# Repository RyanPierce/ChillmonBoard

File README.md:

ChillmonBoard
=============

Chillmon Board

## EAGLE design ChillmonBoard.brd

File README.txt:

Chillmon Board v0.1
Copyright 2013 Ryan Pierce, rdpierce@pobox.com
https://github.com/RyanPierce/ChillmonBoard

Component RASPBERRYPI_B / RASBERRYPI_SHIELD modified from microBuilder
library, available at
http://www.microbuilder.eu/Projects/EagleFootprintLibrary.aspx

OVERVIEW

This board is a Raspberry Pi shield designed to be used with the Chillmon
application, available on Github at https://github.com/eastein/chillmon for 
the purposes of providing temperature control for fermenting beer!

INPUTS

J1-J8 are analog temperature sensors. The center pin is the signal, and the
end pins are power (+3.3V) and Ground. Power is indicated with the + 
symbol.

Each sensor connects to a channel on an MCP3008 10-bit ADC. This is 
connected to the Raspberry Pi as per the Adafruit tutorial available
here: http://learn.adafruit.com/send-raspberry-pi-data-to-cosm
Note that 4 of the Pi's GPIO pins are used for bit-banging SPI; the Pi's
native SPI is not used.

JP1 is a 0.1" header to determine the Vref voltage for the ADC conversion.
Two choices are provided; jumpering the left two pins provides a precision
1.0V reference, while jumpering the right two pins connects the 3.3V power
supply from the Pi. The regulation of this power supply is unknown. Using
1.0V leads to a lower temperature range (maximum is 50C / 122F) but provides
for a higher temperature resolution.

JP9 is a port for a chain of Dallas Semiconductor OneWire temperature
sensors, especially the DS18B20. Adafruit provides a tutorial here:
http://learn.adafruit.com/adafruits-raspberry-pi-lesson-11-ds18b20-temperature-sensing
As above, the center pin is the signal, and the end pins are power and 
ground. Power is marked with a + symbol. Many DS18B20's can be connected in
parallel. Note that the Adafruit Occidentalis distribution for the Raspberry
Pi includes the OneWire kernel driver. At present, the Chillmon software
does not support this. The board includes the 4.7k pullup resistor, which
is required for OneWire.

OUTPUTS

J10, J11, and J12 are digital outputs connected to GPIO pins on the Pi,
specifically GPIO17, GPIO21 (for Rev1 Pi) / GPIO27 (for Rev2 Pi), and
GPIO22 respectively. Rumor has it that the change between Rev1 and Rev2
is corrected within the Python library. Each pin has a 10k pulldown resistor, 
which is critical because the Pi initializes all pins in input mode; voltage
on them can float high enough to trigger solid state relays, which will
quickly burn out an  air conditioner compressor. Currently, the Chillmon
software assumes an air conditioner is connected to J10, however in the
future we would like to add a heater, as we have found that the temperature
at Pumping Station: One in the winter often drops below our target ale
fermenting temperature. Note that these outputs are current limited by the
Pi; it can directly drive a solid state relay.

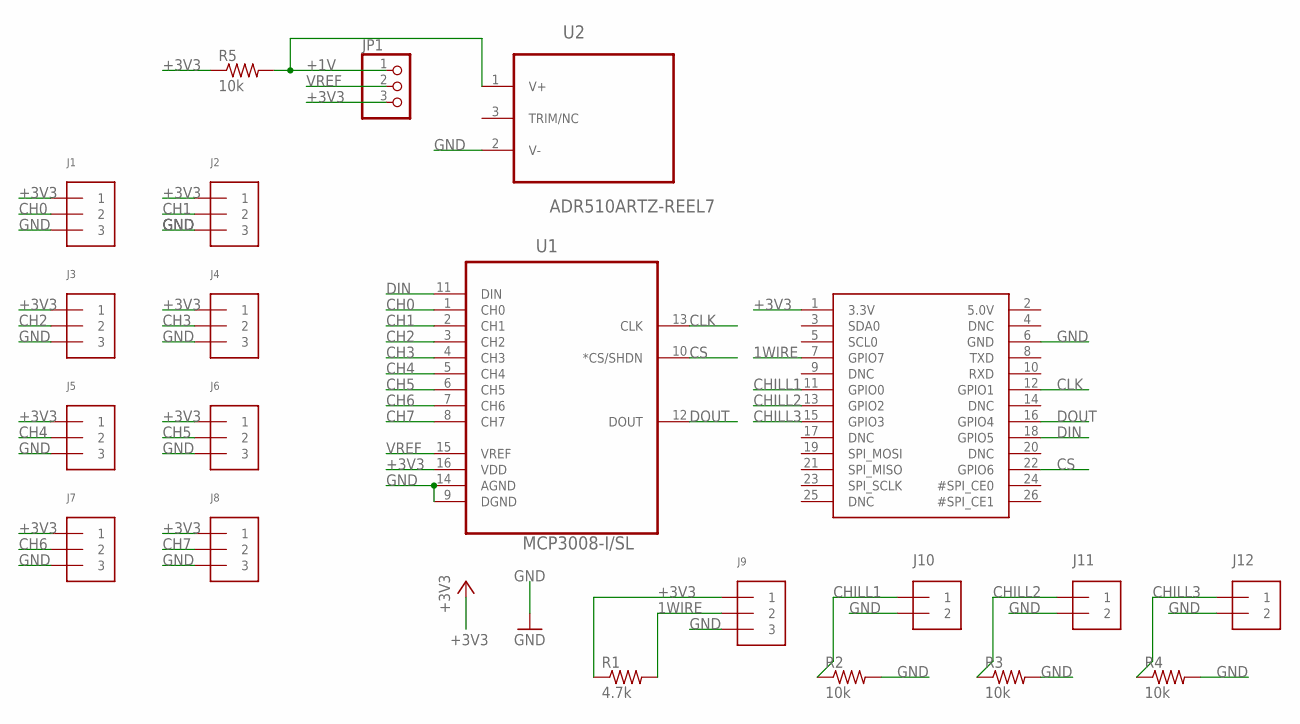
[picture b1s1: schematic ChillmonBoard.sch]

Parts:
J1, J2, J3, J4, J5, J6, J7, J8, J9: TERMBLOCK_1X3; TERMBLOCK_1X3-3.5MM
J10, J11, J12: 1X2-3.5MM
JP1: PINHD-1X3; 1X03
R1: 4.7k; R0805
R2, R3, R4, R5: 10k; R0805
U1: MCP3008-I/SL; SOIC127P600X175-16N
U2: ADR510ARTZ-REEL7; SOT95P237X112-3N
U$1: RASPBERRYPI_BB; RASBERRYPI_SHIELD

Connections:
1WIRE: J9.2, R1.2, U$1.7 (GPIO7)
+1V: JP1.1, R5.2, U2.1 (V+)
+3V3: J1.1, J2.1, J3.1, J4.1, J5.1, J6.1, J7.1, J8.1, J9.1, JP1.3, R1.1, R5.1, U1.16 (VDD), U$1.1 (3.3V)
CH0: J1.2, U1.1 (CH0)
CH1: J2.2, U1.2 (CH1)
CH2: J3.2, U1.3 (CH2)
CH3: J4.2, U1.4 (CH3)
CH4: J5.2, U1.5 (CH4)
CH5: J6.2, U1.6 (CH5)
CH6: J7.2, U1.7 (CH6)
CH7: J8.2, U1.8 (CH7)
CHILL1: J10.1, R2.1, U$1.11 (GPIO0)
CHILL2: J11.1, R3.1, U$1.13 (GPIO2)
CHILL3: J12.1, R4.1, U$1.15 (GPIO3)
CLK: U1.13 (CLK), U$1.12 (GPIO1)
CS: U1.10 (*CS/SHDN), U$1.22 (GPIO6)
DIN: U1.11 (DIN), U$1.18 (GPIO5)
DOUT: U1.12 (DOUT), U$1.16 (GPIO4)
GND: J1.3, J2.3, J3.3, J4.3, J5.3, J6.3, J7.3, J8.3, J9.3, J10.2, J11.2, J12.2, R2.2, R3.2, R4.2, U1.9 (DGND), U1.14 (AGND), U2.2 (V-), U$1.6 (GND)
VREF: JP1.2, U1.15 (VREF)

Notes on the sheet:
J10
J11
J12

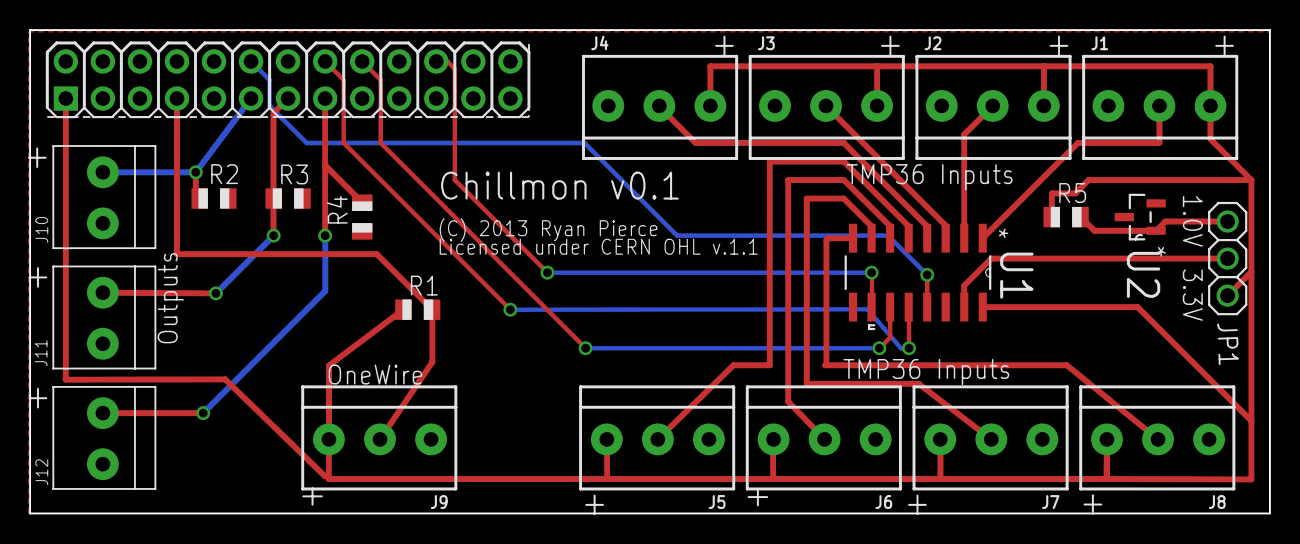
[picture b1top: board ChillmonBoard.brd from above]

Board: 2 copper layers, 85.0 x 33.1 mm, 21 parts (0 on the bottom side), 20 nets.

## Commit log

2013-03-11 Initial version
2013-03-11 Copied microBuilder Raspberry Pi shield, which I'd modified, to Chillmon.lbr
2013-03-12 Updated documentation for Rev1 vs. Rev2 Pi board changes. Added BOM.xls Made board a bit more pretty.
2013-03-12 Updated BOM to include mini jumper
2013-03-13 Changed routing of power to R1
2013-03-13 Updated BOM

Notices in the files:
ChillmonBoard.brd:
(C) 2013 Ryan Pierce
Licensed under CERN OHL v.1.1
parts and their libraries:
microbuilder: This work is placed in the public domain, and may be freely used for commercial and non-commercial work with the following conditions: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
